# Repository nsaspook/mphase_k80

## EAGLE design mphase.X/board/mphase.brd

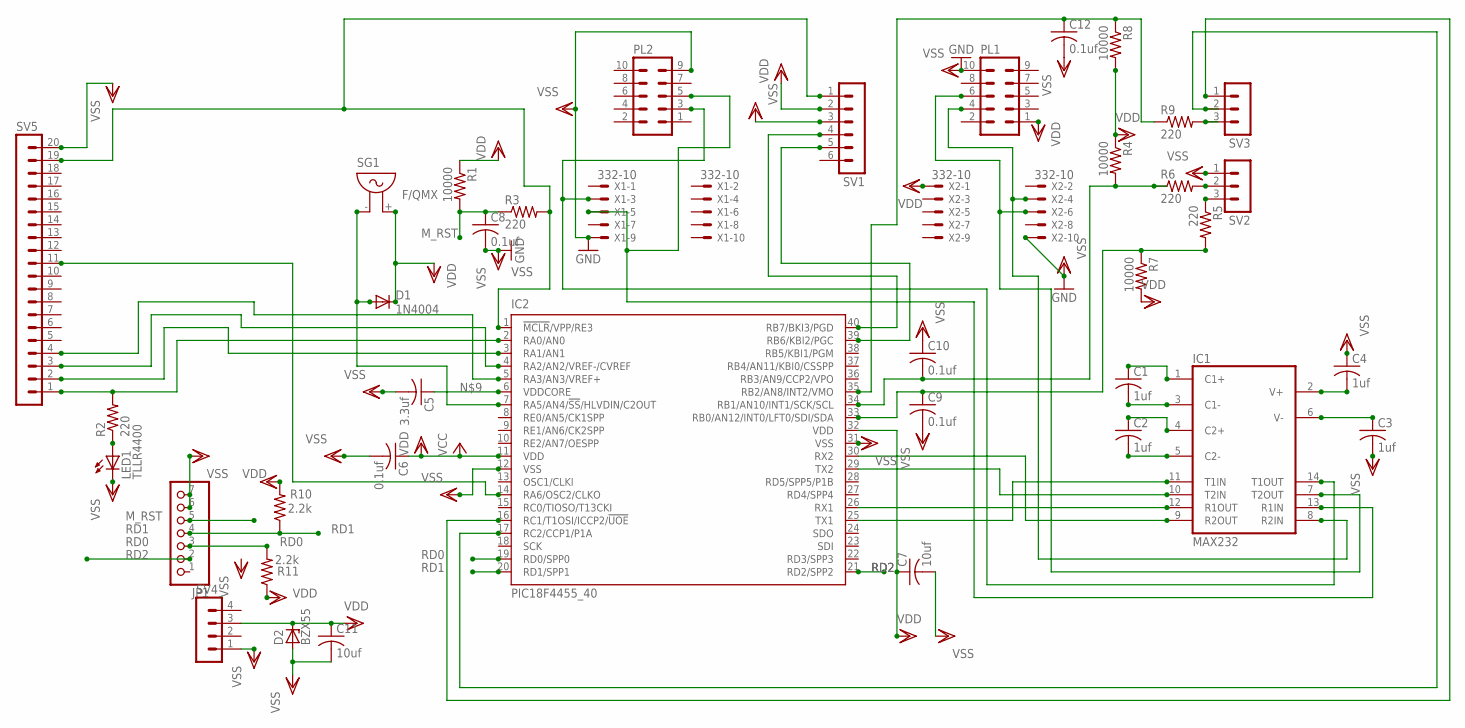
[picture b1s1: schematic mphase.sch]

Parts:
C1, C2, C3, C4: 1uf; C1206
C5: 3.3uf; C1206
C6, C8, C9, C10, C12: 0.1uf; C1206
C7, C11: 10uf; C1206
D1: 1N4004; DO41-10
D2: BZX55; DO35Z10
IC1: MAX232; DIL16
IC2: PIC18F4455_40; DIL40; MPN PIC18F45K80
JP1: PINHD-1X7; 1X07
LED1: TLLR4400; LED3MM
PL1, PL2: 10H
R1, R4, R7, R8: 10000; 0204V
R2, R3, R5, R6, R9: 220; 0204V
R10, R11: 2.2k; 0204V
SG1: F/QMX
SV1: MA06-1
SV2, SV3: MA03-1
SV4: MA04-1
SV5: MA20-1
X1, X2: 332-10

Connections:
M_RST: C8.1, JP1.5, R1.2, R3.1
unnamed: C1.2, IC1.3 (C1-)
unnamed: C2.2, IC1.5 (C2-)
unnamed: C2.1, IC1.4 (C2+)
unnamed: C1.1, IC1.1 (C1+)
unnamed: C4.2, IC1.2 (V+)
unnamed: C3.1, IC1.6 (V-)
unnamed: D1.A, IC2.7 (RA5/AN4/!SS!/HLVDIN/C2OUT), SG1.- (1)
unnamed: IC2.1 (!MCLR!/VPP/RE3), R3.2, SV1.1, SV5.19
unnamed: C5.1, IC2.6 (VDDCORE)
unnamed: IC1.10 (T2IN), IC2.29 (TX2)
unnamed: IC1.11 (T1IN), IC2.25 (TX1)
unnamed: IC1.12 (R1OUT), IC2.26 (RX1)
unnamed: IC1.9 (R2OUT), IC2.30 (RX2)
unnamed: IC2.2 (RA0/AN0), R2.2, SV5.1
unnamed: IC1.7 (T2OUT), PL1.6, X2.6
unnamed: IC1.8 (R2IN), PL1.4, X2.4
unnamed: LED1.A, R2.1
unnamed: IC1.14 (T1OUT), PL2.3, X1.3
unnamed: IC1.13 (R1IN), PL2.5, X1.5
unnamed: C10.2, IC2.34 (RB1/AN10/INT1/SCK/SCL), R4.2, R6.1
unnamed: C9.1, IC2.33 (RB0/AN12/INT0/LFT0/SDI/SDA), R5.2, R7.1
unnamed: IC2.3 (RA1/AN1), SV5.2
unnamed: R6.2, SV2.2
unnamed: R5.1, SV2.3
unnamed: IC2.4 (RA2/AN2/VREF-/CVREF), SV5.3
unnamed: IC2.5 (RA3/AN3/VREF+), SV5.4
unnamed: C12.1, IC2.35 (RB2/AN8/INT2/VMO), R8.1, R9.1
unnamed: IC2.40 (RB7/BKI3/PGD), SV1.4
unnamed: IC2.14 (RA6/OSC2/CLKO), SV5.11
unnamed: R9.2, SV3.3
unnamed: IC2.39 (RB6/KBI2/PGC), SV1.5
unnamed: IC2.16 (RC1/T1OSI/ICCP2/!UOE), SV3.1
unnamed: IC2.17 (RC2/CCP1/P1A), SV3.2
RD0: IC2.19 (RD0/SPP0), JP1.3, R11.2
RD1: IC2.20 (RD1/SPP1), JP1.4, R10.1
RD2: IC2.21 (RD2/SPP2), JP1.2
VCC: C6.1, IC1.16 (VCC), IC2.11 (VDD)
VDD: C7.1, C11.1, D1.C, D2.C, IC2.32 (VDD), PL1.1, R1.1, R4.1, R7.2, R8.2, R10.2, R11.1, SG1.+ (2), SV1.2, SV4.3, X2.1
VSS: C3.2, C4.1, C5.2, C6.2, C7.2, C8.2, C9.2, C10.1, C11.2, C12.2, D2.A, IC1.15 (GND), IC2.12 (VSS), IC2.31 (VSS), JP1.6, JP1.7, LED1.K (C), PL1.10, PL2.9, SV1.3, SV2.1, SV4.1, SV5.20, X1.9, X2.10

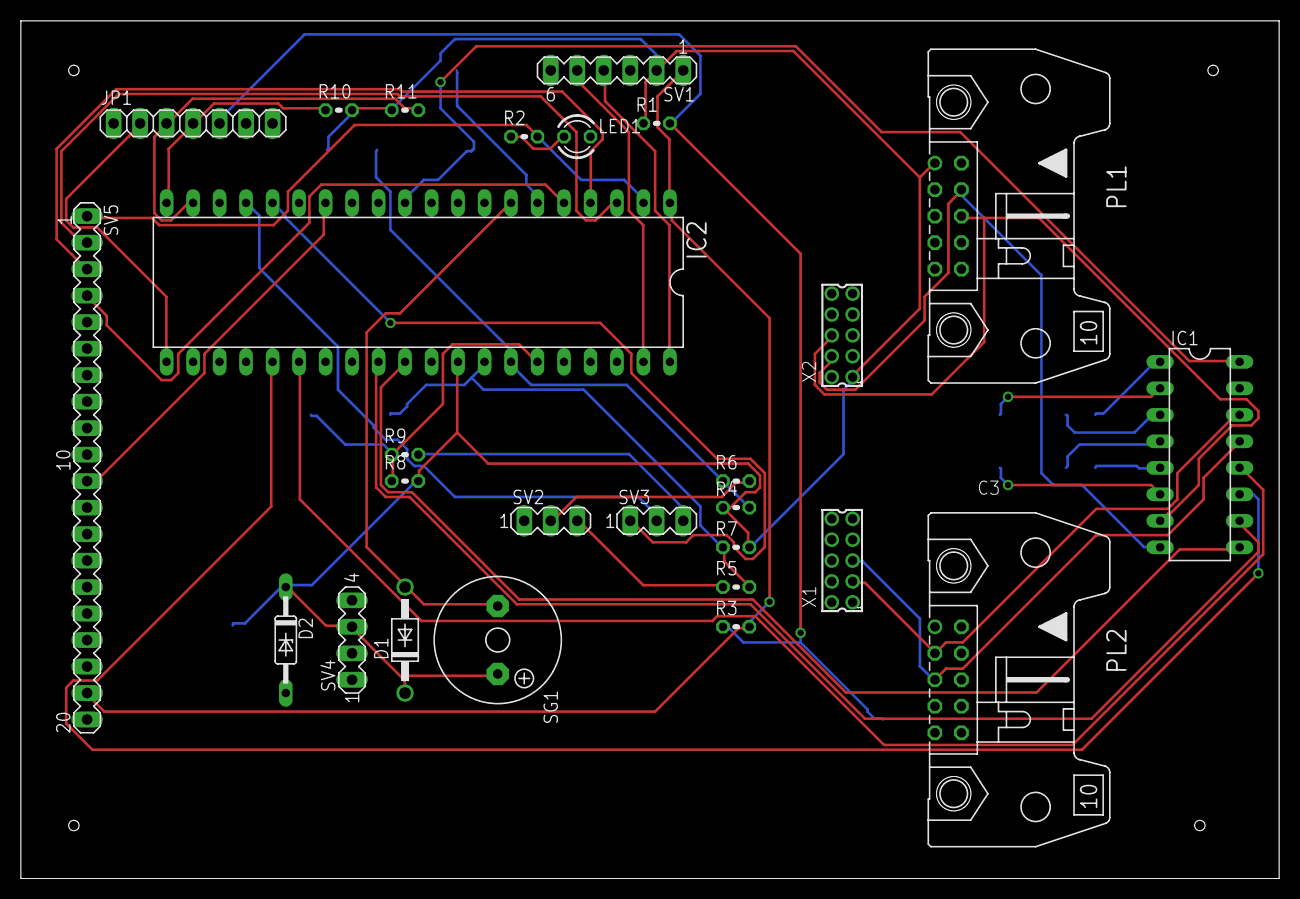
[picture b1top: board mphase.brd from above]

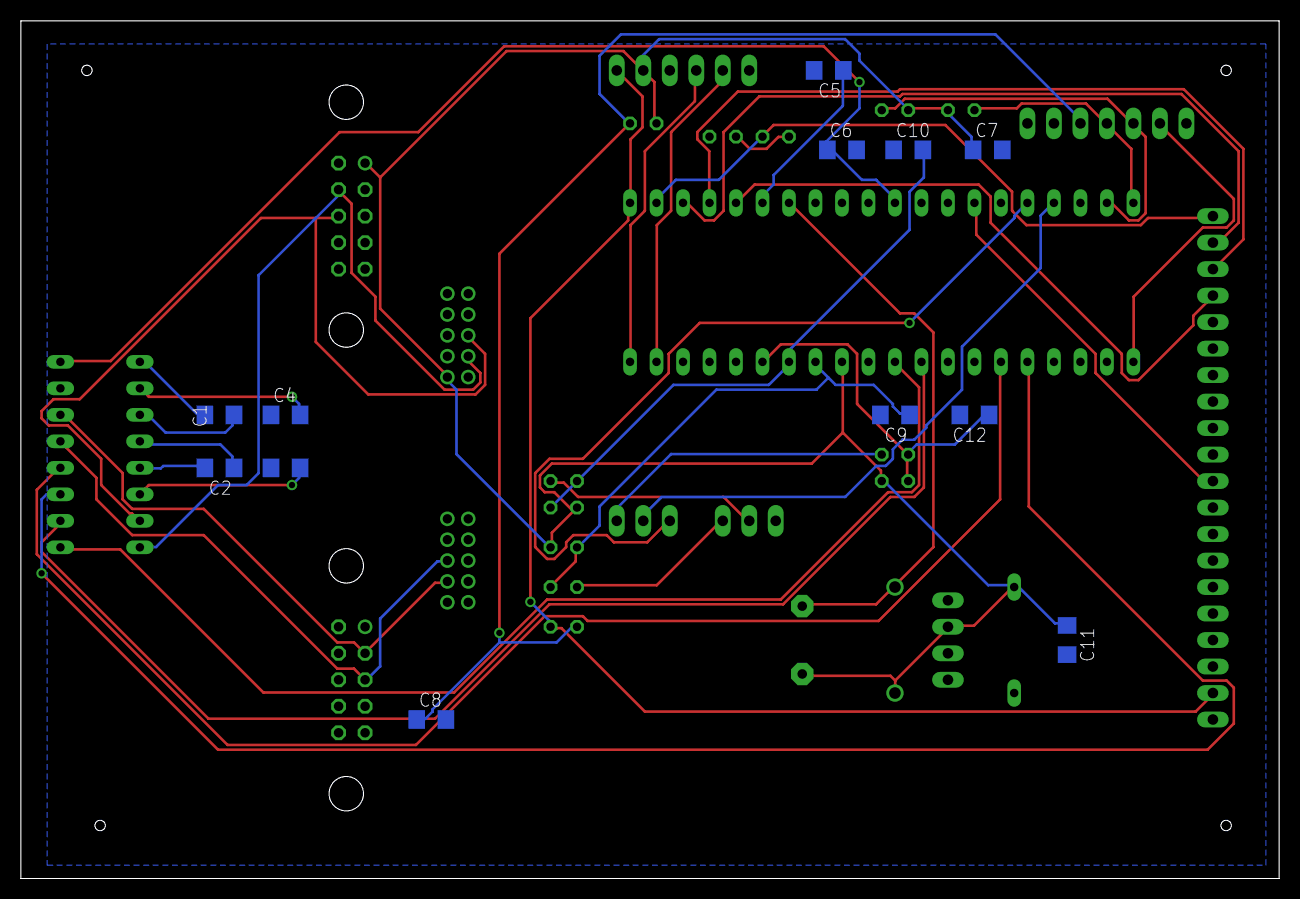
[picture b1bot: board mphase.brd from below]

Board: 2 copper layers, 120.6 x 82.2 mm, 39 parts (12 on the bottom side), 40 nets.
